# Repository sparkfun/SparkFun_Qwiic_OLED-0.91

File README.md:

SparkFun Qwiic OLED Display (0.91", 128x32)
========================================

[*SparkFun Qwiic OLED Display (0.91", 128x32) [LCD-24606]*](https://www.sparkfun.com/products/24606)

The SparkFun Qwiic OLED Display can display up to three lines of text and features 128x32 pixels in a small 0.91” (diagonal) frame. As an OLED, this display does not have a back light layer (unlike LCDs) and therefore it’s thinner, consumes less power, and has higher contrast. 

Thanks to an I<sup>2</sup>C command structure, the board's firmware maintains speed by updating only the part of the screen that changes. This is the same concept use with "Dirty Rectangles" or "Bit blit" operations in computer graphics. 

Version 1.1 of the Qwiic OLED display includes 2x vertical Qwiic connectors populated on the back of the board to easily mount the board and keep the wires inside of the enclosure. Note that the two mounting holes have also been moved to one side of the board. 

Repository Contents
-------------------

* **/Hardware** - Eagle design files (.brd, .sch)
* **/Production** - Production panel files (.brd)

Documentation
--------------
* **[Library](https://docs.sparkfun.com/SparkFun_Qwiic_OLED_Arduino_Library/)** - Arduino library for the Qwiic OLED Display (0.91", 128x32).
* **[Hookup Guide](https://docs.sparkfun.com/SparkFun_Qwiic_OLED_Arduino_Library/)** - Basic hookup guide for the Qwiic OLED Display (0.91", 128x32).

Product Versions
----------------
* [LCD-24606](https://www.sparkfun.com/products/24606) - Initial release, v1.1

Version History
---------------
* v1.1 - Initial release

License Information
-------------------

This product is _**open source**_! 

Please review the LICENSE.md file for license information. 

If you have any questions or concerns on licensing, please contact technical support on our [SparkFun forums](https://forum.sparkfun.com/viewforum.php?f=152).

Distributed as-is; no warranty is given.

- Your friends at SparkFun.

_<COLLABORATION CREDIT>_

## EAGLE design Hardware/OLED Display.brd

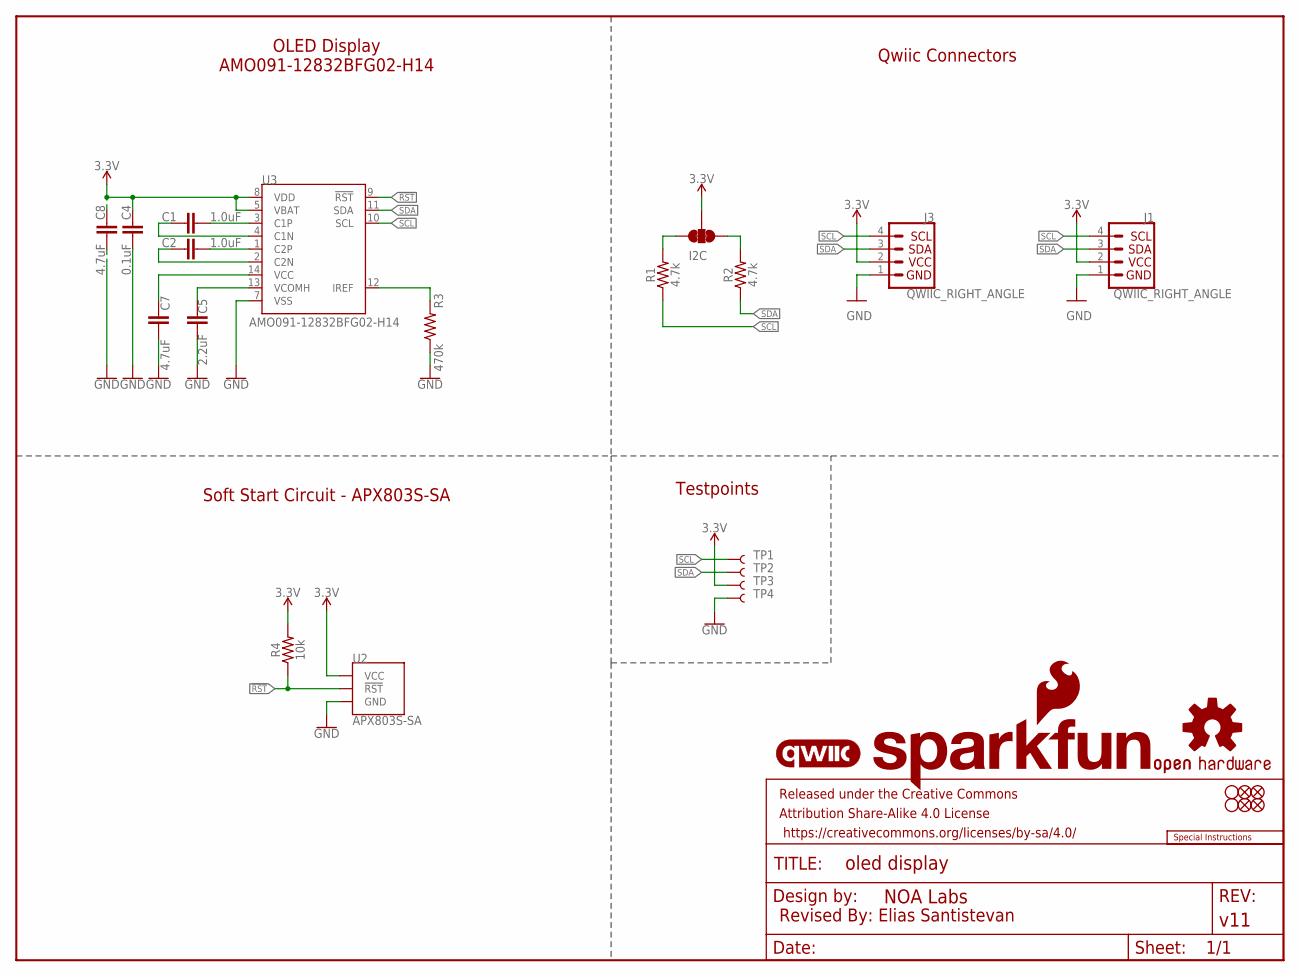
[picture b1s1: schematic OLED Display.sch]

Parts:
C1, C2: 1.0uF; 0603
C4: 0.1uF; 0603
C5: 2.2uF; 0603
C7, C8: 4.7uF; 0603
FD1, FD2, FD3, FD4: FIDUCIAL1X2; FIDUCIAL-1X2
FRAME2: FRAME-LETTER; CREATIVE_COMMONS
H1, H2: STAND-OFFTIGHT; STAND-OFF-TIGHT
I2C: JUMPER-SMT_3_2-NC_TRACE_SILK; SMT-JUMPER_3_2-NC_TRACE_SILK
J1, J3: QWIIC_RIGHT_ANGLE; JST04_1MM_RA
LOGO1: SFE_LOGO_NAME_FLAME.1_INCH; SFE_LOGO_NAME_FLAME_.1
LOGO2: OSHW-LOGOMINI; OSHW-LOGO-MINI
LOGO3: QWIIC_LOGO_4MM; QWIIC_4MM
LOGO4: SPECIAL_INSTRUCTIONS-ORDERING; ORDERING_INSTRUCTIONS
R1, R2: 4.7k; 0603
R3: 470k; 0603
R4: 10k; 0603
TP1, TP2, TP3, TP4: TEST-POINT3X4; PAD.03X.04
U2: APX803S-SA; SOT23-3
U3: AMO091-12832BFG02-H14

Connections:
3.3V: C4.1, C8.2, I2C.2, J1.2, J3.2, R4.2, TP3.1, U2.3 (VCC), U3.5 (VBAT), U3.8 (VDD)
!RST!: R4.1, U2.2 (!RST!), U3.9 (!RST!)
GND: C4.2, C5.2, C7.1, C8.1, J1.1, J3.1, R3.1, TP4.1, U2.1 (GND), U3.7 (VSS)
unnamed: C2.2, U3.1 (C2P)
unnamed: C1.1, U3.4 (C1N)
unnamed: C1.2, U3.3 (C1P)
unnamed: I2C.3, R1.2
unnamed: C5.1, U3.13 (VCOMH)
unnamed: C7.2, U3.14 (VCC)
unnamed: I2C.1, R2.2
unnamed: R3.2, U3.12 (IREF)
unnamed: C2.1, U3.2 (C2N)
SCL: J1.4, J3.4, R1.1, TP1.1, U3.10 (SCL)
SDA: J1.3, J3.3, R2.1, TP2.1, U3.11 (SDA)

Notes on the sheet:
Revised By: Elias Santistevan
Qwiic Connectors
OLED Display AMO091-12832BFG02-H14
Soft Start Circuit - APX803S-SA
Testpoints

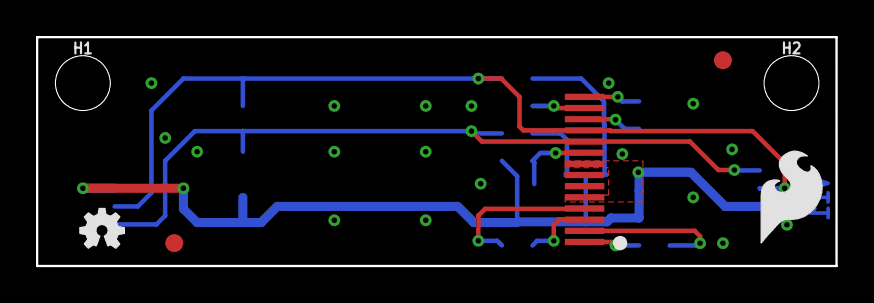
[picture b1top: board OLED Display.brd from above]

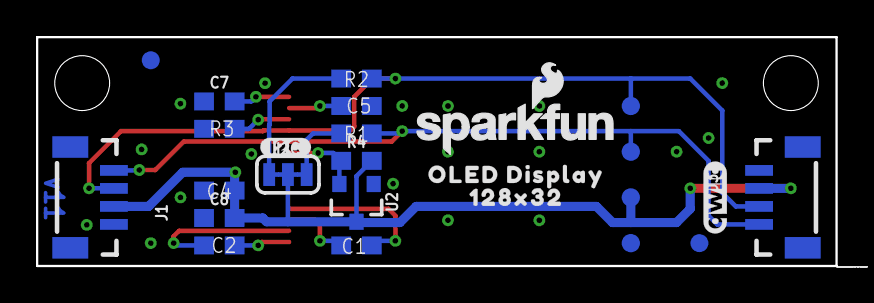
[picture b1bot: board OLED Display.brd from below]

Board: 2 copper layers, 44.4 x 12.7 mm, 34 parts (25 on the bottom side), 14 nets.

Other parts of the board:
U$1: SFE_LOGO_FLAME_.2
U$2: OLED_DISPLAY94
U$3: 128X3295
U$4: #I2C#16

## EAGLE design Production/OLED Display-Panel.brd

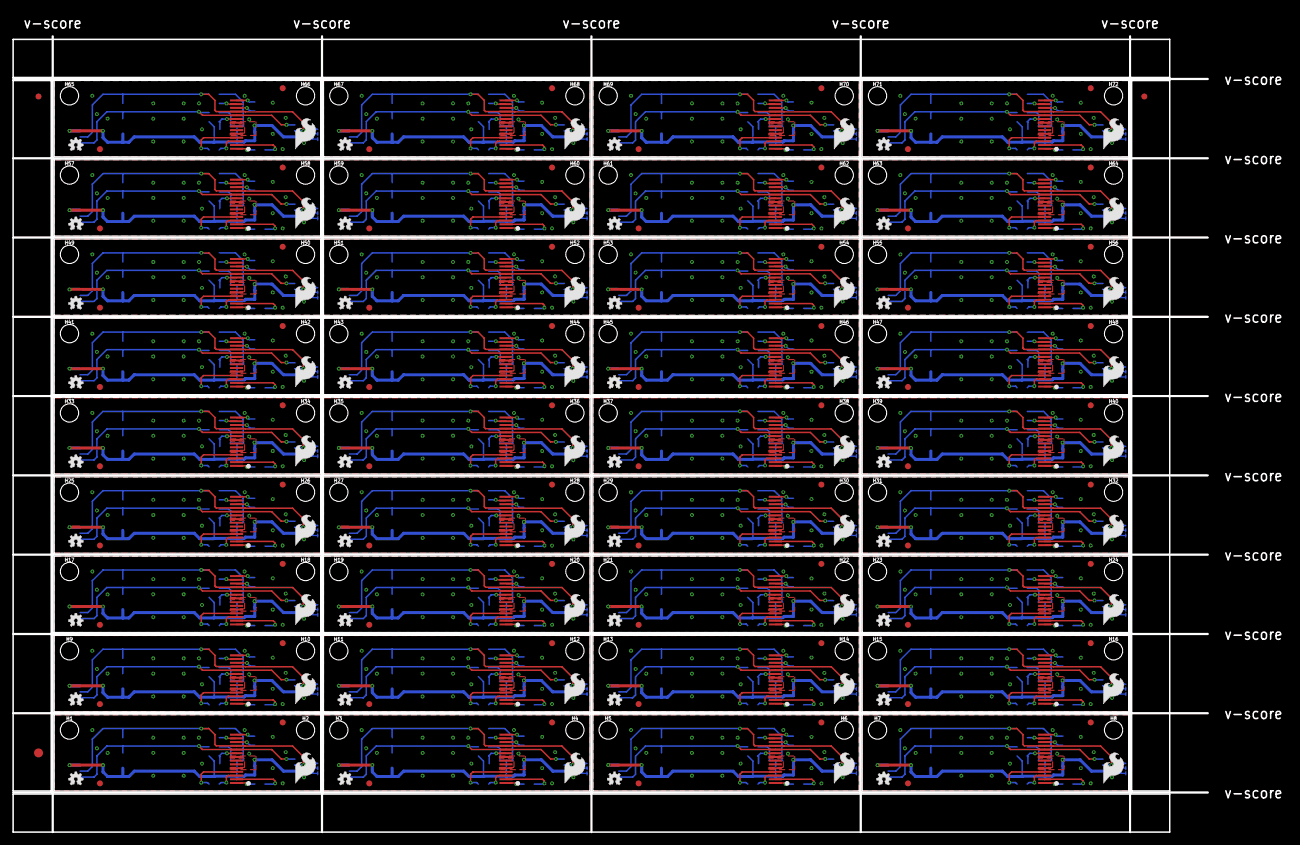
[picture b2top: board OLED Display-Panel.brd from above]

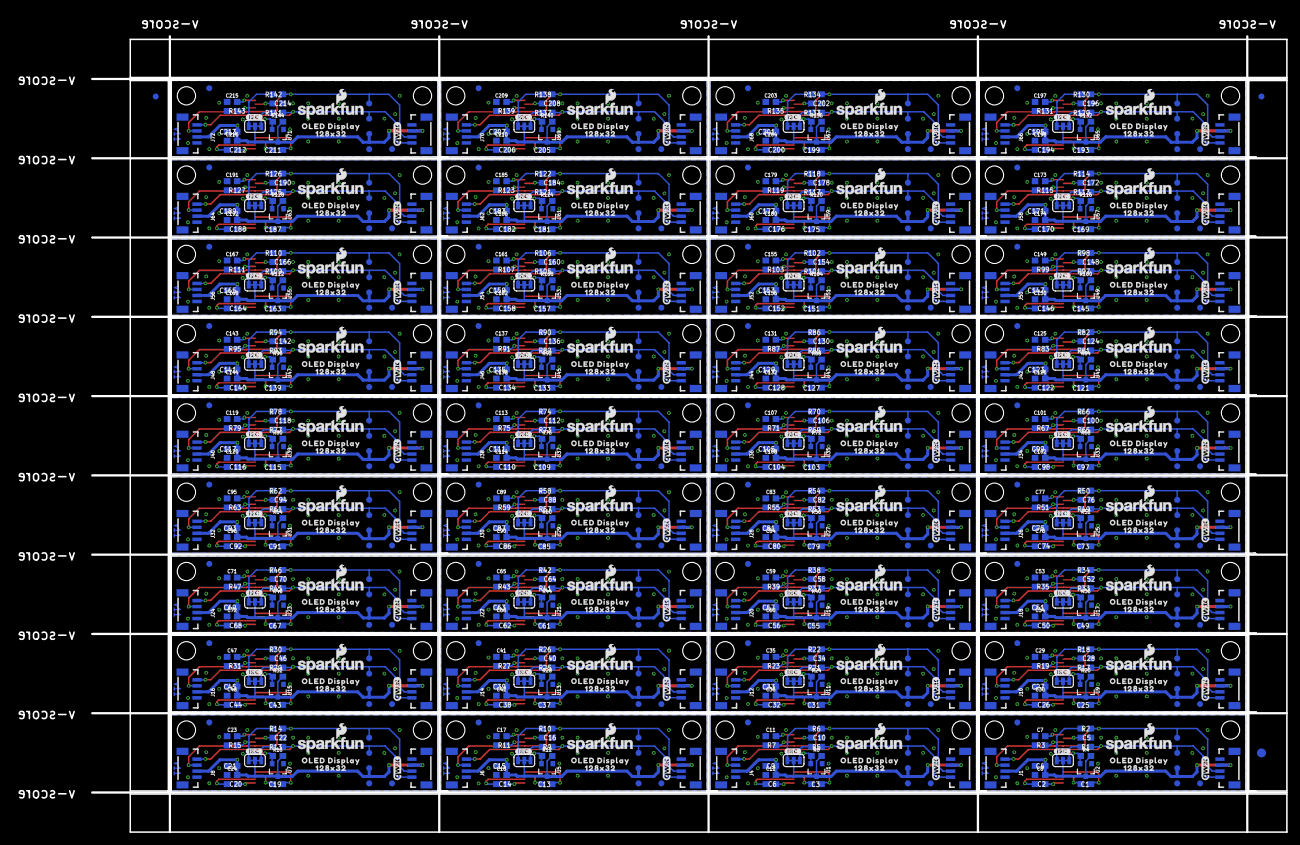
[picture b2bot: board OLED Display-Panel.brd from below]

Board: 2 copper layers, 212.4 x 136.6 mm, 1158 parts (903 on the bottom side), 504 nets.

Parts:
C1, C2, C3, C6, C13, C14, C19, C20, C25, C26, C31, C32, C37, C38, C43, C44, C49, C50, C55, C56, C61, C62, C67, C68, C73, C74, C79, C80, C85, C86, C91, C92, C97, C98, C103, C104, C109, C110, C115, C116, C121, C122, C127, C128, C133, C134, C139, C140, C145, C146, C151, C152, C157, C158, C163, C164, C169, C170, C175, C176, C181, C182, C187, C188, C193, C194, C199, C200, C205, C206, C211, C212: 1.0uF; 0603
C4, C9, C15, C21, C27, C33, C39, C45, C51, C57, C63, C69, C75, C81, C87, C93, C99, C105, C111, C117, C123, C129, C135, C141, C147, C153, C159, C165, C171, C177, C183, C189, C195, C201, C207, C213: 0.1uF; 0603
C5, C10, C16, C22, C28, C34, C40, C46, C52, C58, C64, C70, C76, C82, C88, C94, C100, C106, C112, C118, C124, C130, C136, C142, C148, C154, C160, C166, C172, C178, C184, C190, C196, C202, C208, C214: 2.2uF; 0603
C7, C8, C11, C12, C17, C18, C23, C24, C29, C30, C35, C36, C41, C42, C47, C48, C53, C54, C59, C60, C65, C66, C71, C72, C77, C78, C83, C84, C89, C90, C95, C96, C101, C102, C107, C108, C113, C114, C119, C120, C125, C126, C131, C132, C137, C138, C143, C144, C149, C150, C155, C156, C161, C162, C167, C168, C173, C174, C179, C180, C185, C186, C191, C192, C197, C198, C203, C204, C209, C210, C215, C216: 4.7uF; 0603
E$1, E$2, E$3, E$4: FIDUCIAL-1X2
E$5, E$6: FIDUCIAL-1.5X3
FD1, FD2, FD3, FD4, FD5, FD6, FD7, FD8, FD9, FD10, FD11, FD12, FD13, FD14, FD15, FD16, FD17, FD18, FD19, FD20, FD21, FD22, FD23, FD24, FD25, FD26, FD27, FD28, FD29, FD30, FD31, FD32, FD33, FD34, FD35, FD36, FD37, FD38, FD39, FD40, FD41, FD42, FD43, FD44, FD45, FD46, FD47, FD48, FD49, FD50, FD51, FD52, FD53, FD54, FD55, FD56, FD57, FD58, FD59, FD60, FD61, FD62, FD63, FD64, FD65, FD66, FD67, FD68, FD69, FD70, FD71, FD72, FD73, FD74, FD75, FD76, FD77, FD78, FD79, FD80, FD81, FD82, FD83, FD84, FD85, FD86, FD87, FD88, FD89, FD90, FD91, FD92, FD93, FD94, FD95, FD96, FD97, FD98, FD99, FD100, FD101, FD102, FD103, FD104, FD105, FD106, FD107, FD108, FD109, FD110, FD111, FD112, FD113, FD114, FD115, FD116, FD117, FD118, FD119, FD120, FD121, FD122, FD123, FD124, FD125, FD126, FD127, FD128, FD129, FD130, FD131, FD132, FD133, FD134, FD135, FD136, FD137, FD138, FD139, FD140, FD141, FD142, FD143, FD144: FIDUCIAL1X2; FIDUCIAL-1X2
H1, H2, H3, H4, H5, H6, H7, H8, H9, H10, H11, H12, H13, H14, H15, H16, H17, H18, H19, H20, H21, H22, H23, H24, H25, H26, H27, H28, H29, H30, H31, H32, H33, H34, H35, H36, H37, H38, H39, H40, H41, H42, H43, H44, H45, H46, H47, H48, H49, H50, H51, H52, H53, H54, H55, H56, H57, H58, H59, H60, H61, H62, H63, H64, H65, H66, H67, H68, H69, H70, H71, H72: STAND-OFFTIGHT; STAND-OFF-TIGHT
I2C, I2C1, I2C2, I2C3, I2C4, I2C5, I2C6, I2C7, I2C8, I2C9, I2C10, I2C11, I2C12, I2C13, I2C14, I2C15, I2C16, I2C17, I2C18, I2C19, I2C20, I2C21, I2C22, I2C23, I2C24, I2C25, I2C26, I2C27, I2C28, I2C29, I2C30, I2C31, I2C32, I2C33, I2C34, I2C35: JUMPER-SMT_3_2-NC_TRACE_SILK; SMT-JUMPER_3_2-NC_TRACE_SILK
J1, J2, J3, J4, J5, J6, J7, J8, J9, J10, J11, J12, J13, J14, J15, J16, J17, J18, J19, J20, J21, J22, J23, J24, J25, J26, J27, J28, J29, J30, J31, J32, J33, J34, J35, J36, J37, J38, J39, J40, J41, J42, J43, J44, J45, J46, J47, J48, J49, J50, J51, J52, J53, J54, J55, J56, J57, J58, J59, J60, J61, J62, J63, J64, J65, J66, J67, J68, J69, J70, J71, J72: Vertical Qwiic Connector; JST04_1MM_VERT
LOGO1, LOGO6, LOGO9, LOGO12, LOGO15, LOGO18, LOGO21, LOGO24, LOGO27, LOGO30, LOGO33, LOGO36, LOGO39, LOGO42, LOGO45, LOGO48, LOGO51, LOGO54, LOGO57, LOGO60, LOGO63, LOGO66, LOGO69, LOGO72, LOGO75, LOGO78, LOGO81, LOGO84, LOGO87, LOGO90, LOGO93, LOGO96, LOGO99, LOGO102, LOGO105, LOGO108: SFE_LOGO_NAME_FLAME.1_INCH; SFE_LOGO_NAME_FLAME_.1
LOGO2, LOGO4, LOGO7, LOGO10, LOGO13, LOGO16, LOGO19, LOGO22, LOGO25, LOGO28, LOGO31, LOGO34, LOGO37, LOGO40, LOGO43, LOGO46, LOGO49, LOGO52, LOGO55, LOGO58, LOGO61, LOGO64, LOGO67, LOGO70, LOGO73, LOGO76, LOGO79, LOGO82, LOGO85, LOGO88, LOGO91, LOGO94, LOGO97, LOGO100, LOGO103, LOGO106: OSHW-LOGOMINI; OSHW-LOGO-MINI
LOGO3, LOGO5, LOGO8, LOGO11, LOGO14, LOGO17, LOGO20, LOGO23, LOGO26, LOGO29, LOGO32, LOGO35, LOGO38, LOGO41, LOGO44, LOGO47, LOGO50, LOGO53, LOGO56, LOGO59, LOGO62, LOGO65, LOGO68, LOGO71, LOGO74, LOGO77, LOGO80, LOGO83, LOGO86, LOGO89, LOGO92, LOGO95, LOGO98, LOGO101, LOGO104, LOGO107: QWIIC_LOGO_4MM; QWIIC_4MM
R1, R2, R5, R6, R9, R10, R13, R14, R17, R18, R21, R22, R25, R26, R29, R30, R33, R34, R37, R38, R41, R42, R45, R46, R49, R50, R53, R54, R57, R58, R61, R62, R65, R66, R69, R70, R73, R74, R77, R78, R81, R82, R85, R86, R89, R90, R93, R94, R97, R98, R101, R102, R105, R106, R109, R110, R113, R114, R117, R118, R121, R122, R125, R126, R129, R130, R133, R134, R137, R138, R141, R142: 4.7k; 0603
R3, R7, R11, R15, R19, R23, R27, R31, R35, R39, R43, R47, R51, R55, R59, R63, R67, R71, R75, R79, R83, R87, R91, R95, R99, R103, R107, R111, R115, R119, R123, R127, R131, R135, R139, R143: 470k; 0603
R4, R8, R12, R16, R20, R24, R28, R32, R36, R40, R44, R48, R52, R56, R60, R64, R68, R72, R76, R80, R84, R88, R92, R96, R100, R104, R108, R112, R116, R120, R124, R128, R132, R136, R140, R144: 10k; 0603
TP1, TP2, TP3, TP4, TP5, TP6, TP7, TP8, TP9, TP10, TP11, TP12, TP13, TP14, TP15, TP16, TP17, TP18, TP19, TP20, TP21, TP22, TP23, TP24, TP25, TP26, TP27, TP28, TP29, TP30, TP31, TP32, TP33, TP34, TP35, TP36, TP37, TP38, TP39, TP40, TP41, TP42, TP43, TP44, TP45, TP46, TP47, TP48, TP49, TP50, TP51, TP52, TP53, TP54, TP55, TP56, TP57, TP58, TP59, TP60, TP61, TP62, TP63, TP64, TP65, TP66, TP67, TP68, TP69, TP70, TP71, TP72, TP73, TP74, TP75, TP76, TP77, TP78, TP79, TP80, TP81, TP82, TP83, TP84, TP85, TP86, TP87, TP88, TP89, TP90, TP91, TP92, TP93, TP94, TP95, TP96, TP97, TP98, TP99, TP100, TP101, TP102, TP103, TP104, TP105, TP106, TP107, TP108, TP109, TP110, TP111, TP112, TP113, TP114, TP115, TP116, TP117, TP118, TP119, TP120, TP121, TP122, TP123, TP124, TP125, TP126, TP127, TP128, TP129, TP130, TP131, TP132, TP133, TP134, TP135, TP136, TP137, TP138, TP139, TP140, TP141, TP142, TP143, TP144: TEST-POINT3X4; PAD.03X.04
U1, U2, U5, U7, U9, U11, U13, U15, U17, U19, U21, U23, U25, U27, U29, U31, U33, U35, U37, U39, U41, U43, U45, U47, U49, U51, U53, U55, U57, U59, U61, U63, U65, U67, U69, U71: APX803S-SA; SOT23-3
U3, U4, U6, U8, U10, U12, U14, U16, U18, U20, U22, U24, U26, U28, U30, U32, U34, U36, U38, U40, U42, U44, U46, U48, U50, U52, U54, U56, U58, U60, U62, U64, U66, U68, U70, U72: AMO091-12832BFG02-H14
U$1, U$5, U$9, U$13, U$17, U$21, U$25, U$29, U$33, U$37, U$41, U$45, U$49, U$53, U$57, U$61, U$65, U$69, U$73, U$77, U$81, U$85, U$89, U$93, U$97, U$101, U$105, U$109, U$113, U$117, U$121, U$125, U$129, U$133, U$137, U$141: SFE_LOGO_FLAME_.2
U$2, U$6, U$10, U$14, U$18, U$22, U$26, U$30, U$34, U$38, U$42, U$46, U$50, U$54, U$58, U$62, U$66, U$70, U$74, U$78, U$82, U$86, U$90, U$94, U$98, U$102, U$106, U$110, U$114, U$118, U$122, U$126, U$130, U$134, U$138, U$142: OLED_DISPLAY94
U$3, U$7, U$11, U$15, U$19, U$23, U$27, U$31, U$35, U$39, U$43, U$47, U$51, U$55, U$59, U$63, U$67, U$71, U$75, U$79, U$83, U$87, U$91, U$95, U$99, U$103, U$107, U$111, U$115, U$119, U$123, U$127, U$131, U$135, U$139, U$143: 128X3295
U$4, U$8, U$12, U$16, U$20, U$24, U$28, U$32, U$36, U$40, U$44, U$48, U$52, U$56, U$60, U$64, U$68, U$72, U$76, U$80, U$84, U$88, U$92, U$96, U$100, U$104, U$108, U$112, U$116, U$120, U$124, U$128, U$132, U$136, U$140, U$144: #I2C#16

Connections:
3.3V: C4.1, C8.2, I2C.2, J1.2, J3.2, R4.2, TP3.1, U2.3, U3.5, U3.8
3.3V1: C9.1, C12.2, I2C1.2, J2.2, J4.2, R8.2, TP7.1, U1.3, U4.5, U4.8
3.3V2: C15.1, C18.2, I2C2.2, J5.2, J6.2, R12.2, TP11.1, U5.3, U6.5, U6.8
3.3V3: C21.1, C24.2, I2C3.2, J7.2, J8.2, R16.2, TP15.1, U7.3, U8.5, U8.8
3.3V4: C27.1, C30.2, I2C4.2, J9.2, J10.2, R20.2, TP19.1, U9.3, U10.5, U10.8
3.3V5: C33.1, C36.2, I2C5.2, J11.2, J12.2, R24.2, TP23.1, U11.3, U12.5, U12.8
3.3V6: C39.1, C42.2, I2C6.2, J13.2, J14.2, R28.2, TP27.1, U13.3, U14.5, U14.8
3.3V7: C45.1, C48.2, I2C7.2, J15.2, J16.2, R32.2, TP31.1, U15.3, U16.5, U16.8
3.3V8: C51.1, C54.2, I2C8.2, J17.2, J18.2, R36.2, TP35.1, U17.3, U18.5, U18.8
3.3V9: C57.1, C60.2, I2C9.2, J19.2, J20.2, R40.2, TP39.1, U19.3, U20.5, U20.8
3.3V10: C63.1, C66.2, I2C10.2, J21.2, J22.2, R44.2, TP43.1, U21.3, U22.5, U22.8
3.3V11: C69.1, C72.2, I2C11.2, J23.2, J24.2, R48.2, TP47.1, U23.3, U24.5, U24.8
3.3V12: C75.1, C78.2, I2C12.2, J25.2, J26.2, R52.2, TP51.1, U25.3, U26.5, U26.8
3.3V13: C81.1, C84.2, I2C13.2, J27.2, J28.2, R56.2, TP55.1, U27.3, U28.5, U28.8
3.3V14: C87.1, C90.2, I2C14.2, J29.2, J30.2, R60.2, TP59.1, U29.3, U30.5, U30.8
3.3V15: C93.1, C96.2, I2C15.2, J31.2, J32.2, R64.2, TP63.1, U31.3, U32.5, U32.8
3.3V16: C99.1, C102.2, I2C16.2, J33.2, J34.2, R68.2, TP67.1, U33.3, U34.5, U34.8
3.3V17: C105.1, C108.2, I2C17.2, J35.2, J36.2, R72.2, TP71.1, U35.3, U36.5, U36.8
3.3V18: C111.1, C114.2, I2C18.2, J37.2, J38.2, R76.2, TP75.1, U37.3, U38.5, U38.8
3.3V19: C117.1, C120.2, I2C19.2, J39.2, J40.2, R80.2, TP79.1, U39.3, U40.5, U40.8
3.3V20: C123.1, C126.2, I2C20.2, J41.2, J42.2, R84.2, TP83.1, U41.3, U42.5, U42.8
3.3V21: C129.1, C132.2, I2C21.2, J43.2, J44.2, R88.2, TP87.1, U43.3, U44.5, U44.8
3.3V22: C135.1, C138.2, I2C22.2, J45.2, J46.2, R92.2, TP91.1, U45.3, U46.5, U46.8
3.3V23: C141.1, C144.2, I2C23.2, J47.2, J48.2, R96.2, TP95.1, U47.3, U48.5, U48.8
3.3V24: C147.1, C150.2, I2C24.2, J49.2, J50.2, R100.2, TP99.1, U49.3, U50.5, U50.8
3.3V25: C153.1, C156.2, I2C25.2, J51.2, J52.2, R104.2, TP103.1, U51.3, U52.5, U52.8
3.3V26: C159.1, C162.2, I2C26.2, J53.2, J54.2, R108.2, TP107.1, U53.3, U54.5, U54.8
3.3V27: C165.1, C168.2, I2C27.2, J55.2, J56.2, R112.2, TP111.1, U55.3, U56.5, U56.8
3.3V28: C171.1, C174.2, I2C28.2, J57.2, J58.2, R116.2, TP115.1, U57.3, U58.5, U58.8
3.3V29: C177.1, C180.2, I2C29.2, J59.2, J60.2, R120.2, TP119.1, U59.3, U60.5, U60.8
3.3V30: C183.1, C186.2, I2C30.2, J61.2, J62.2, R124.2, TP123.1, U61.3, U62.5, U62.8
3.3V31: C189.1, C192.2, I2C31.2, J63.2, J64.2, R128.2, TP127.1, U63.3, U64.5, U64.8
3.3V32: C195.1, C198.2, I2C32.2, J65.2, J66.2, R132.2, TP131.1, U65.3, U66.5, U66.8
3.3V33: C201.1, C204.2, I2C33.2, J67.2, J68.2, R136.2, TP135.1, U67.3, U68.5, U68.8
3.3V34: C207.1, C210.2, I2C34.2, J69.2, J70.2, R140.2, TP139.1, U69.3, U70.5, U70.8
3.3V35: C213.1, C216.2, I2C35.2, J71.2, J72.2, R144.2, TP143.1, U71.3, U72.5, U72.8
!RST!: R4.1, U2.2, U3.9
!RST!1: R8.1, U1.2, U4.9
!RST!2: R12.1, U5.2, U6.9
!RST!3: R16.1, U7.2, U8.9
!RST!4: R20.1, U9.2, U10.9
!RST!5: R24.1, U11.2, U12.9
!RST!6: R28.1, U13.2, U14.9
!RST!7: R32.1, U15.2, U16.9
!RST!8: R36.1, U17.2, U18.9
!RST!9: R40.1, U19.2, U20.9
!RST!10: R44.1, U21.2, U22.9
!RST!11: R48.1, U23.2, U24.9
!RST!12: R52.1, U25.2, U26.9
!RST!13: R56.1, U27.2, U28.9
!RST!14: R60.1, U29.2, U30.9
!RST!15: R64.1, U31.2, U32.9
!RST!16: R68.1, U33.2, U34.9
!RST!17: R72.1, U35.2, U36.9
!RST!18: R76.1, U37.2, U38.9
!RST!19: R80.1, U39.2, U40.9
!RST!20: R84.1, U41.2, U42.9
!RST!21: R88.1, U43.2, U44.9
!RST!22: R92.1, U45.2, U46.9
!RST!23: R96.1, U47.2, U48.9
!RST!24: R100.1, U49.2, U50.9
!RST!25: R104.1, U51.2, U52.9
!RST!26: R108.1, U53.2, U54.9
!RST!27: R112.1, U55.2, U56.9
!RST!28: R116.1, U57.2, U58.9
!RST!29: R120.1, U59.2, U60.9
!RST!30: R124.1, U61.2, U62.9
!RST!31: R128.1, U63.2, U64.9
!RST!32: R132.1, U65.2, U66.9
!RST!33: R136.1, U67.2, U68.9
!RST!34: R140.1, U69.2, U70.9
!RST!35: R144.1, U71.2, U72.9
GND: C4.2, C5.2, C7.1, C8.1, J1.1, J3.1, R3.1, TP4.1, U2.1, U3.7
GND1: C9.2, C10.2, C11.1, C12.1, J2.1, J4.1, R7.1, TP8.1, U1.1, U4.7
GND2: C15.2, C16.2, C17.1, C18.1, J5.1, J6.1, R11.1, TP12.1, U5.1, U6.7
GND3: C21.2, C22.2, C23.1, C24.1, J7.1, J8.1, R15.1, TP16.1, U7.1, U8.7
GND4: C27.2, C28.2, C29.1, C30.1, J9.1, J10.1, R19.1, TP20.1, U9.1, U10.7
GND5: C33.2, C34.2, C35.1, C36.1, J11.1, J12.1, R23.1, TP24.1, U11.1, U12.7
GND6: C39.2, C40.2, C41.1, C42.1, J13.1, J14.1, R27.1, TP28.1, U13.1, U14.7
GND7: C45.2, C46.2, C47.1, C48.1, J15.1, J16.1, R31.1, TP32.1, U15.1, U16.7
GND8: C51.2, C52.2, C53.1, C54.1, J17.1, J18.1, R35.1, TP36.1, U17.1, U18.7
GND9: C57.2, C58.2, C59.1, C60.1, J19.1, J20.1, R39.1, TP40.1, U19.1, U20.7
GND10: C63.2, C64.2, C65.1, C66.1, J21.1, J22.1, R43.1, TP44.1, U21.1, U22.7
GND11: C69.2, C70.2, C71.1, C72.1, J23.1, J24.1, R47.1, TP48.1, U23.1, U24.7
GND12: C75.2, C76.2, C77.1, C78.1, J25.1, J26.1, R51.1, TP52.1, U25.1, U26.7
GND13: C81.2, C82.2, C83.1, C84.1, J27.1, J28.1, R55.1, TP56.1, U27.1, U28.7
GND14: C87.2, C88.2, C89.1, C90.1, J29.1, J30.1, R59.1, TP60.1, U29.1, U30.7
GND15: C93.2, C94.2, C95.1, C96.1, J31.1, J32.1, R63.1, TP64.1, U31.1, U32.7
GND16: C99.2, C100.2, C101.1, C102.1, J33.1, J34.1, R67.1, TP68.1, U33.1, U34.7
GND17: C105.2, C106.2, C107.1, C108.1, J35.1, J36.1, R71.1, TP72.1, U35.1, U36.7
GND18: C111.2, C112.2, C113.1, C114.1, J37.1, J38.1, R75.1, TP76.1, U37.1, U38.7
GND19: C117.2, C118.2, C119.1, C120.1, J39.1, J40.1, R79.1, TP80.1, U39.1, U40.7
GND20: C123.2, C124.2, C125.1, C126.1, J41.1, J42.1, R83.1, TP84.1, U41.1, U42.7
GND21: C129.2, C130.2, C131.1, C132.1, J43.1, J44.1, R87.1, TP88.1, U43.1, U44.7
GND22: C135.2, C136.2, C137.1, C138.1, J45.1, J46.1, R91.1, TP92.1, U45.1, U46.7
GND23: C141.2, C142.2, C143.1, C144.1, J47.1, J48.1, R95.1, TP96.1, U47.1, U48.7
GND24: C147.2, C148.2, C149.1, C150.1, J49.1, J50.1, R99.1, TP100.1, U49.1, U50.7
GND25: C153.2, C154.2, C155.1, C156.1, J51.1, J52.1, R103.1, TP104.1, U51.1, U52.7
GND26: C159.2, C160.2, C161.1, C162.1, J53.1, J54.1, R107.1, TP108.1, U53.1, U54.7
GND27: C165.2, C166.2, C167.1, C168.1, J55.1, J56.1, R111.1, TP112.1, U55.1, U56.7
GND28: C171.2, C172.2, C173.1, C174.1, J57.1, J58.1, R115.1, TP116.1, U57.1, U58.7
GND29: C177.2, C178.2, C179.1, C180.1, J59.1, J60.1, R119.1, TP120.1, U59.1, U60.7
GND30: C183.2, C184.2, C185.1, C186.1, J61.1, J62.1, R123.1, TP124.1, U61.1, U62.7
GND31: C189.2, C190.2, C191.1, C192.1, J63.1, J64.1, R127.1, TP128.1, U63.1, U64.7
GND32: C195.2, C196.2, C197.1, C198.1, J65.1, J66.1, R131.1, TP132.1, U65.1, U66.7
GND33: C201.2, C202.2, C203.1, C204.1, J67.1, J68.1, R135.1, TP136.1, U67.1, U68.7
GND34: C207.2, C208.2, C209.1, C210.1, J69.1, J70.1, R139.1, TP140.1, U69.1, U70.7
GND35: C213.2, C214.2, C215.1, C216.1, J71.1, J72.1, R143.1, TP144.1, U71.1, U72.7
unnamed: C2.2, U3.1
unnamed: C1.1, U3.4
unnamed: C3.1, U4.4
unnamed: C1.2, U3.3
unnamed: I2C.3, R1.2
unnamed: C5.1, U3.13
unnamed: C7.2, U3.14
unnamed: I2C.1, R2.2
unnamed: R3.2, U3.12
unnamed: R7.2, U4.12
unnamed: C10.1, U4.13
unnamed: C11.2, U4.14
unnamed: I2C1.3, R5.2
unnamed: I2C1.1, R6.2
unnamed: C6.2, U4.1
unnamed: C3.2, U4.3
unnamed: C2.1, U3.2
unnamed: C6.1, U4.2
unnamed: C13.1, U6.4
unnamed: R11.2, U6.12
unnamed: C16.1, U6.13
unnamed: C17.2, U6.14
unnamed: I2C2.3, R9.2
unnamed: I2C2.1, R10.2
unnamed: C14.2, U6.1
unnamed: C13.2, U6.3
unnamed: C14.1, U6.2
unnamed: C19.1, U8.4
unnamed: R15.2, U8.12
unnamed: C22.1, U8.13
unnamed: C23.2, U8.14
unnamed: I2C3.3, R13.2
unnamed: I2C3.1, R14.2
unnamed: C20.2, U8.1
unnamed: C19.2, U8.3
unnamed: C20.1, U8.2
unnamed: C25.1, U10.4
unnamed: R19.2, U10.12
unnamed: C28.1, U10.13
unnamed: C29.2, U10.14
unnamed: I2C4.3, R17.2
unnamed: I2C4.1, R18.2
unnamed: C26.2, U10.1
unnamed: C25.2, U10.3
unnamed: C26.1, U10.2
unnamed: C31.1, U12.4
unnamed: R23.2, U12.12
unnamed: C34.1, U12.13
unnamed: C35.2, U12.14
unnamed: I2C5.3, R21.2
unnamed: I2C5.1, R22.2
unnamed: C32.2, U12.1
unnamed: C31.2, U12.3
unnamed: C32.1, U12.2
unnamed: C37.1, U14.4
unnamed: R27.2, U14.12
unnamed: C40.1, U14.13
unnamed: C41.2, U14.14
unnamed: I2C6.3, R25.2
unnamed: I2C6.1, R26.2
unnamed: C38.2, U14.1
unnamed: C37.2, U14.3
unnamed: C38.1, U14.2
unnamed: C43.1, U16.4
unnamed: R31.2, U16.12
unnamed: C46.1, U16.13
unnamed: C47.2, U16.14
unnamed: I2C7.3, R29.2
unnamed: I2C7.1, R30.2
unnamed: C44.2, U16.1
unnamed: C43.2, U16.3
unnamed: C44.1, U16.2
unnamed: C49.1, U18.4
unnamed: R35.2, U18.12
unnamed: C52.1, U18.13
unnamed: C53.2, U18.14
unnamed: I2C8.3, R33.2
unnamed: I2C8.1, R34.2
unnamed: C50.2, U18.1
unnamed: C49.2, U18.3
unnamed: C50.1, U18.2
unnamed: C55.1, U20.4
unnamed: R39.2, U20.12
unnamed: C58.1, U20.13
unnamed: C59.2, U20.14
unnamed: I2C9.3, R37.2
unnamed: I2C9.1, R38.2
unnamed: C56.2, U20.1
unnamed: C55.2, U20.3
unnamed: C56.1, U20.2
unnamed: C61.1, U22.4
unnamed: R43.2, U22.12
unnamed: C64.1, U22.13
unnamed: C65.2, U22.14
unnamed: I2C10.3, R41.2
unnamed: I2C10.1, R42.2
unnamed: C62.2, U22.1
unnamed: C61.2, U22.3
unnamed: C62.1, U22.2
unnamed: C67.1, U24.4
unnamed: R47.2, U24.12
unnamed: C70.1, U24.13
unnamed: C71.2, U24.14
unnamed: I2C11.3, R45.2
unnamed: I2C11.1, R46.2
unnamed: C68.2, U24.1
unnamed: C67.2, U24.3
unnamed: C68.1, U24.2
unnamed: C73.1, U26.4
unnamed: R51.2, U26.12
unnamed: C76.1, U26.13
unnamed: C77.2, U26.14
unnamed: I2C12.3, R49.2
unnamed: I2C12.1, R50.2
unnamed: C74.2, U26.1
unnamed: C73.2, U26.3
unnamed: C74.1, U26.2
unnamed: C79.1, U28.4
unnamed: R55.2, U28.12
unnamed: C82.1, U28.13
unnamed: C83.2, U28.14
unnamed: I2C13.3, R53.2
unnamed: I2C13.1, R54.2
unnamed: C80.2, U28.1
unnamed: C79.2, U28.3
unnamed: C80.1, U28.2
unnamed: C85.1, U30.4
unnamed: R59.2, U30.12
unnamed: C88.1, U30.13
unnamed: C89.2, U30.14
unnamed: I2C14.3, R57.2
unnamed: I2C14.1, R58.2
unnamed: C86.2, U30.1
unnamed: C85.2, U30.3
unnamed: C86.1, U30.2
unnamed: C91.1, U32.4
unnamed: R63.2, U32.12
unnamed: C94.1, U32.13
unnamed: C95.2, U32.14
unnamed: I2C15.3, R61.2
unnamed: I2C15.1, R62.2
unnamed: C92.2, U32.1
unnamed: C91.2, U32.3
unnamed: C92.1, U32.2
unnamed: C97.1, U34.4
unnamed: R67.2, U34.12
unnamed: C100.1, U34.13
unnamed: C101.2, U34.14
unnamed: I2C16.3, R65.2
unnamed: I2C16.1, R66.2
unnamed: C98.2, U34.1
unnamed: C97.2, U34.3
unnamed: C98.1, U34.2
unnamed: C103.1, U36.4
unnamed: R71.2, U36.12
unnamed: C106.1, U36.13
unnamed: C107.2, U36.14
unnamed: I2C17.3, R69.2
unnamed: I2C17.1, R70.2
unnamed: C104.2, U36.1
unnamed: C103.2, U36.3
unnamed: C104.1, U36.2
unnamed: C109.1, U38.4
unnamed: R75.2, U38.12
unnamed: C112.1, U38.13
unnamed: C113.2, U38.14
unnamed: I2C18.3, R73.2
unnamed: I2C18.1, R74.2
unnamed: C110.2, U38.1
unnamed: C109.2, U38.3
unnamed: C110.1, U38.2
unnamed: C115.1, U40.4
unnamed: R79.2, U40.12
unnamed: C118.1, U40.13
unnamed: C119.2, U40.14
unnamed: I2C19.3, R77.2
unnamed: I2C19.1, R78.2
unnamed: C116.2, U40.1
unnamed: C115.2, U40.3
unnamed: C116.1, U40.2
unnamed: C121.1, U42.4
unnamed: R83.2, U42.12
unnamed: C124.1, U42.13
unnamed: C125.2, U42.14
unnamed: I2C20.3, R81.2
unnamed: I2C20.1, R82.2
unnamed: C122.2, U42.1
unnamed: C121.2, U42.3
unnamed: C122.1, U42.2
unnamed: C127.1, U44.4
unnamed: R87.2, U44.12
unnamed: C130.1, U44.13
unnamed: C131.2, U44.14
unnamed: I2C21.3, R85.2
unnamed: I2C21.1, R86.2
unnamed: C128.2, U44.1
unnamed: C127.2, U44.3
unnamed: C128.1, U44.2
unnamed: C133.1, U46.4
unnamed: R91.2, U46.12
unnamed: C136.1, U46.13
unnamed: C137.2, U46.14
unnamed: I2C22.3, R89.2
unnamed: I2C22.1, R90.2
unnamed: C134.2, U46.1
unnamed: C133.2, U46.3
unnamed: C134.1, U46.2
unnamed: C139.1, U48.4
unnamed: R95.2, U48.12
unnamed: C142.1, U48.13
unnamed: C143.2, U48.14
unnamed: I2C23.3, R93.2
unnamed: I2C23.1, R94.2
unnamed: C140.2, U48.1
unnamed: C139.2, U48.3
unnamed: C140.1, U48.2
unnamed: C145.1, U50.4
unnamed: R99.2, U50.12
unnamed: C148.1, U50.13
unnamed: C149.2, U50.14
unnamed: I2C24.3, R97.2
unnamed: I2C24.1, R98.2
unnamed: C146.2, U50.1
unnamed: C145.2, U50.3
unnamed: C146.1, U50.2
unnamed: C151.1, U52.4
unnamed: R103.2, U52.12
unnamed: C154.1, U52.13
unnamed: C155.2, U52.14
unnamed: I2C25.3, R101.2
unnamed: I2C25.1, R102.2
unnamed: C152.2, U52.1
unnamed: C151.2, U52.3
unnamed: C152.1, U52.2
unnamed: C157.1, U54.4
unnamed: R107.2, U54.12
unnamed: C160.1, U54.13
unnamed: C161.2, U54.14
unnamed: I2C26.3, R105.2
unnamed: I2C26.1, R106.2
unnamed: C158.2, U54.1
unnamed: C157.2, U54.3
unnamed: C158.1, U54.2
unnamed: C163.1, U56.4
unnamed: R111.2, U56.12
unnamed: C166.1, U56.13
unnamed: C167.2, U56.14
unnamed: I2C27.3, R109.2
unnamed: I2C27.1, R110.2
unnamed: C164.2, U56.1
unnamed: C163.2, U56.3
unnamed: C164.1, U56.2
unnamed: C169.1, U58.4
unnamed: R115.2, U58.12
unnamed: C172.1, U58.13
unnamed: C173.2, U58.14
unnamed: I2C28.3, R113.2
unnamed: I2C28.1, R114.2
unnamed: C170.2, U58.1
unnamed: C169.2, U58.3
unnamed: C170.1, U58.2
unnamed: C175.1, U60.4
unnamed: R119.2, U60.12
unnamed: C178.1, U60.13
unnamed: C179.2, U60.14
unnamed: I2C29.3, R117.2
unnamed: I2C29.1, R118.2
unnamed: C176.2, U60.1
unnamed: C175.2, U60.3
unnamed: C176.1, U60.2
unnamed: C181.1, U62.4
unnamed: R123.2, U62.12
unnamed: C184.1, U62.13
unnamed: C185.2, U62.14
unnamed: I2C30.3, R121.2
unnamed: I2C30.1, R122.2
unnamed: C182.2, U62.1
unnamed: C181.2, U62.3
unnamed: C182.1, U62.2
unnamed: C187.1, U64.4
unnamed: R127.2, U64.12
unnamed: C190.1, U64.13
unnamed: C191.2, U64.14
unnamed: I2C31.3, R125.2
unnamed: I2C31.1, R126.2
unnamed: C188.2, U64.1
unnamed: C187.2, U64.3
unnamed: C188.1, U64.2
unnamed: C193.1, U66.4
unnamed: R131.2, U66.12
unnamed: C196.1, U66.13
unnamed: C197.2, U66.14
unnamed: I2C32.3, R129.2
unnamed: I2C32.1, R130.2
unnamed: C194.2, U66.1
unnamed: C193.2, U66.3
unnamed: C194.1, U66.2
unnamed: C199.1, U68.4
unnamed: R135.2, U68.12
unnamed: C202.1, U68.13
unnamed: C203.2, U68.14
unnamed: I2C33.3, R133.2
unnamed: I2C33.1, R134.2
unnamed: C200.2, U68.1
unnamed: C199.2, U68.3
unnamed: C200.1, U68.2
unnamed: C205.1, U70.4
unnamed: R139.2, U70.12
unnamed: C208.1, U70.13
unnamed: C209.2, U70.14
unnamed: I2C34.3, R137.2
unnamed: I2C34.1, R138.2
unnamed: C206.2, U70.1
unnamed: C205.2, U70.3
unnamed: C206.1, U70.2
unnamed: C211.1, U72.4
unnamed: R143.2, U72.12
unnamed: C214.1, U72.13
unnamed: C215.2, U72.14
unnamed: I2C35.3, R141.2
unnamed: I2C35.1, R142.2
unnamed: C212.2, U72.1
unnamed: C211.2, U72.3
unnamed: C212.1, U72.2
SCL: J1.4, J3.4, R1.1, TP1.1, U3.10
SCL1: J2.4, J4.4, R5.1, TP5.1, U4.10
SCL2: J5.4, J6.4, R9.1, TP9.1, U6.10
SCL3: J7.4, J8.4, R13.1, TP13.1, U8.10
SCL4: J9.4, J10.4, R17.1, TP17.1, U10.10
SCL5: J11.4, J12.4, R21.1, TP21.1, U12.10
SCL6: J13.4, J14.4, R25.1, TP25.1, U14.10
SCL7: J15.4, J16.4, R29.1, TP29.1, U16.10
SCL8: J17.4, J18.4, R33.1, TP33.1, U18.10
SCL9: J19.4, J20.4, R37.1, TP37.1, U20.10
SCL10: J21.4, J22.4, R41.1, TP41.1, U22.10
SCL11: J23.4, J24.4, R45.1, TP45.1, U24.10
SCL12: J25.4, J26.4, R49.1, TP49.1, U26.10
SCL13: J27.4, J28.4, R53.1, TP53.1, U28.10
SCL14: J29.4, J30.4, R57.1, TP57.1, U30.10
SCL15: J31.4, J32.4, R61.1, TP61.1, U32.10
SCL16: J33.4, J34.4, R65.1, TP65.1, U34.10
SCL17: J35.4, J36.4, R69.1, TP69.1, U36.10
SCL18: J37.4, J38.4, R73.1, TP73.1, U38.10
SCL19: J39.4, J40.4, R77.1, TP77.1, U40.10
SCL20: J41.4, J42.4, R81.1, TP81.1, U42.10
SCL21: J43.4, J44.4, R85.1, TP85.1, U44.10
SCL22: J45.4, J46.4, R89.1, TP89.1, U46.10
SCL23: J47.4, J48.4, R93.1, TP93.1, U48.10
SCL24: J49.4, J50.4, R97.1, TP97.1, U50.10
SCL25: J51.4, J52.4, R101.1, TP101.1, U52.10
SCL26: J53.4, J54.4, R105.1, TP105.1, U54.10
SCL27: J55.4, J56.4, R109.1, TP109.1, U56.10
SCL28: J57.4, J58.4, R113.1, TP113.1, U58.10
SCL29: J59.4, J60.4, R117.1, TP117.1, U60.10
SCL30: J61.4, J62.4, R121.1, TP121.1, U62.10
SCL31: J63.4, J64.4, R125.1, TP125.1, U64.10
SCL32: J65.4, J66.4, R129.1, TP129.1, U66.10
SCL33: J67.4, J68.4, R133.1, TP133.1, U68.10
SCL34: J69.4, J70.4, R137.1, TP137.1, U70.10
SCL35: J71.4, J72.4, R141.1, TP141.1, U72.10
SDA: J1.3, J3.3, R2.1, TP2.1, U3.11
SDA1: J2.3, J4.3, R6.1, TP6.1, U4.11
SDA2: J5.3, J6.3, R10.1, TP10.1, U6.11
SDA3: J7.3, J8.3, R14.1, TP14.1, U8.11
SDA4: J9.3, J10.3, R18.1, TP18.1, U10.11
SDA5: J11.3, J12.3, R22.1, TP22.1, U12.11
SDA6: J13.3, J14.3, R26.1, TP26.1, U14.11
SDA7: J15.3, J16.3, R30.1, TP30.1, U16.11
SDA8: J17.3, J18.3, R34.1, TP34.1, U18.11
SDA9: J19.3, J20.3, R38.1, TP38.1, U20.11
SDA10: J21.3, J22.3, R42.1, TP42.1, U22.11
SDA11: J23.3, J24.3, R46.1, TP46.1, U24.11
SDA12: J25.3, J26.3, R50.1, TP50.1, U26.11
SDA13: J27.3, J28.3, R54.1, TP54.1, U28.11
SDA14: J29.3, J30.3, R58.1, TP58.1, U30.11
SDA15: J31.3, J32.3, R62.1, TP62.1, U32.11
SDA16: J33.3, J34.3, R66.1, TP66.1, U34.11
SDA17: J35.3, J36.3, R70.1, TP70.1, U36.11
SDA18: J37.3, J38.3, R74.1, TP74.1, U38.11
SDA19: J39.3, J40.3, R78.1, TP78.1, U40.11
SDA20: J41.3, J42.3, R82.1, TP82.1, U42.11
SDA21: J43.3, J44.3, R86.1, TP86.1, U44.11
SDA22: J45.3, J46.3, R90.1, TP90.1, U46.11
SDA23: J47.3, J48.3, R94.1, TP94.1, U48.11
SDA24: J49.3, J50.3, R98.1, TP98.1, U50.11
SDA25: J51.3, J52.3, R102.1, TP102.1, U52.11
SDA26: J53.3, J54.3, R106.1, TP106.1, U54.11
SDA27: J55.3, J56.3, R110.1, TP110.1, U56.11
SDA28: J57.3, J58.3, R114.1, TP114.1, U58.11
SDA29: J59.3, J60.3, R118.1, TP118.1, U60.11
SDA30: J61.3, J62.3, R122.1, TP122.1, U62.11
SDA31: J63.3, J64.3, R126.1, TP126.1, U64.11
SDA32: J65.3, J66.3, R130.1, TP130.1, U66.11
SDA33: J67.3, J68.3, R134.1, TP134.1, U68.11
SDA34: J69.3, J70.3, R138.1, TP138.1, U70.11
SDA35: J71.3, J72.3, R142.1, TP142.1, U72.11

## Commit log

2023-12-08 Uploads Original Design
2023-12-08 Replaces parts not in the SparkFun Eagle Libraries, adds logos, moves qwiic connectors and standoffs
2023-12-08 Replaces more parts
2023-12-08 Changes soft start circuit to RC circuit
2023-12-08 Shrinks the overall size of the board
2023-12-11 Routes the board
2023-12-11 Updates the display device and footprint name, adds version in silk
2023-12-11 Adds label to I2C jumper
2023-12-11 Adds testpoints
2023-12-20 Adds more datasheets, updates part number for OLED display
2023-12-20 Adds more measures
2023-12-20 Adds panel
2023-12-20 Swaps right angle Qwiic connector to vertical
2023-12-20 Repanelizes the design now that it has vertical Qwiic connectors
2023-12-20 Updates zip file to include version
2024-02-14 Set up for files for GitHub Pages tutorial
2024-02-14 Removes datasheet for old display
2024-02-15 OLED Display Highlighted for Tutorial
2024-02-15 Hardware Hookup and Demo Action Shots
2024-02-15 Rearrange paths

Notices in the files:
parts and their libraries:
OSHW-LOGO-M: Licensing: Creative Commons ShareAlike 4.0 International - https://creativecommons.org/licenses/by-sa/4.0
SparkFun-Aesthetics: Released under the Creative Commons Attribution Share-Alike 4.0 License
SparkFun-Aesthetics: https://creativecommons.org/licenses/by-sa/4.0
